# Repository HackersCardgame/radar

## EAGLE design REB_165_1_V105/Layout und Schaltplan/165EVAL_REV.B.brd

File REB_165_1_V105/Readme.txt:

1. Installieren Sie den USB Treiber "Treiber\MCP2200 Windows Driver 2014-10-09\Driver Installation Tool"
Im Windows Geräte Manager finden Sie nun ein neues Gerät mit einem virtuellen COM-Port
2. Installieren Sie die REB165 Software über die Setup.exe (Microsoft .NET Framework 4.0 muss installiert sein)
3. Starten Sie des REB165 Software und verbinden Sie sich mit dem richtigen COM-Port

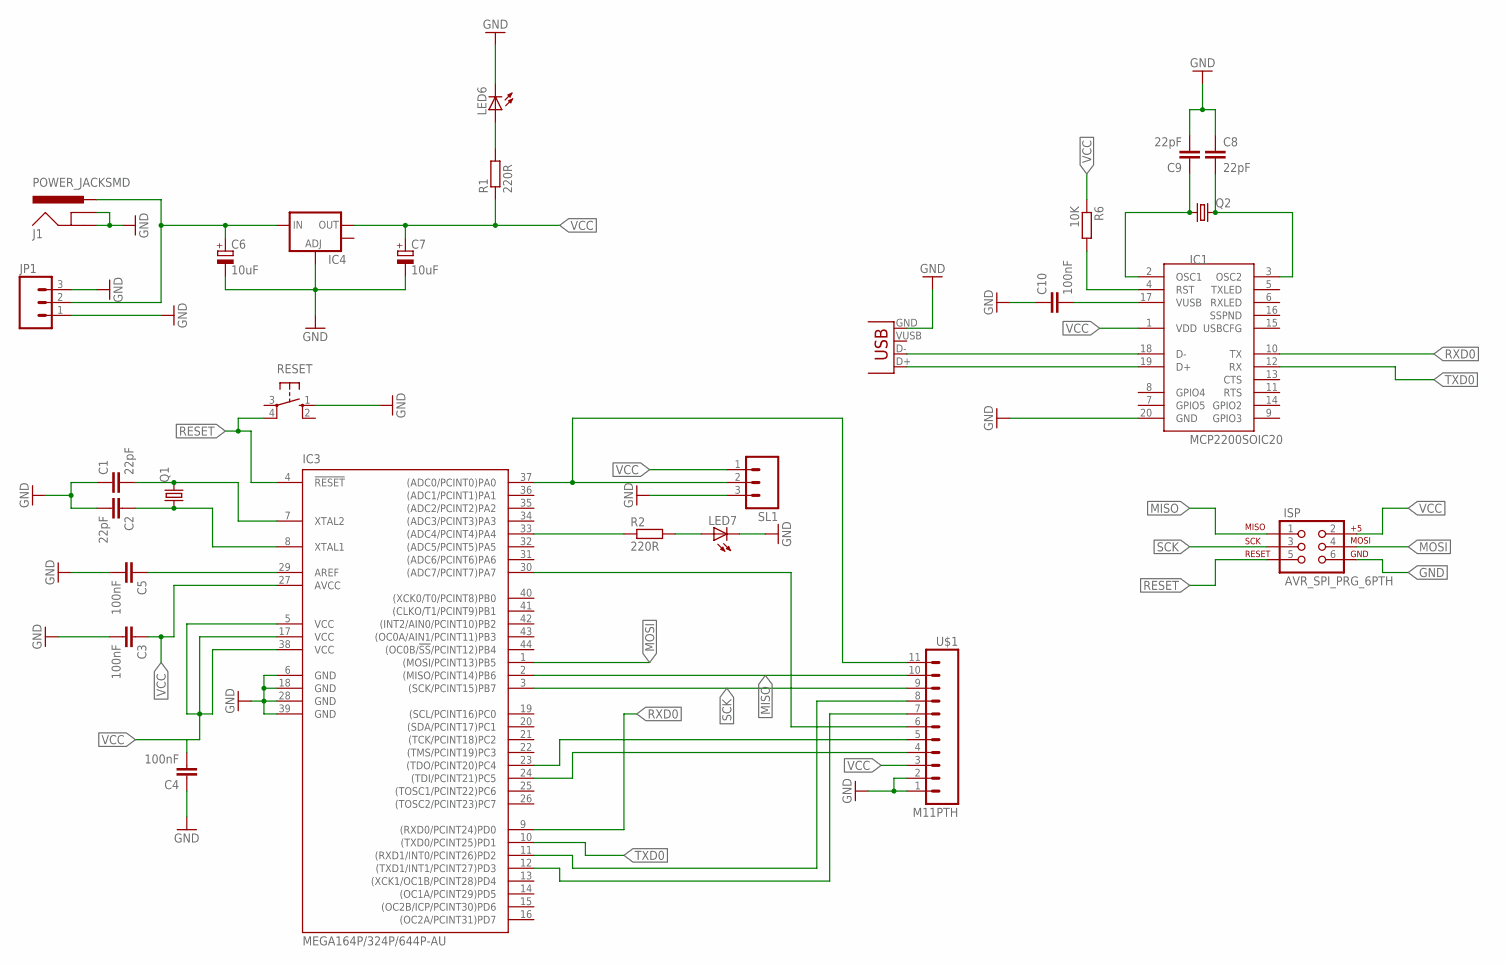
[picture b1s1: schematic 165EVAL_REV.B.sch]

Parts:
C1, C2, C8, C9: 22pF; C0805K
C3, C4, C5, C10: 100nF; C0805K
C6, C7: 10uF; CT6032
IC1: MCP2200SOIC20; SOIC20
IC3: MEGA164P/324P/644P-AU; TQFP44
IC4: V_REG_LM1117SOT223; SOT223
ISP: AVR_SPI_PRG_6PTH; 2X3
J1: POWER_JACKSMD; POWER_JACK_SMD
JP1: M03PTH; 1X03
LED6, LED7: LEDSMT1206; 1206
Q1, Q2: CRYSTALSM49; SM49
R1, R2: 220R; R1206
R6: 10K; R1206
RESET: 10-XX; B3F-10XX
SL1: M03; 03P
U$1: M11PTH; 1X11
USB: USB-B-S; USB-B-SMT

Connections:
GND: C1.1, C2.2, C3.2, C4.1, C5.2, C6.-, C7.-, C8.1, C9.2, C10.1, IC1.20 (GND), IC3.6 (GND), IC3.18 (GND), IC3.28 (GND), IC3.39 (GND), IC4.1 (ADJ), ISP.6, J1.GND (GNDBREAK), J1.P$4 (GND), JP1.1, JP1.3, LED6.C, LED7.C, RESET.1 (S), SL1.3, U$1.1, U$1.2, USB.GND
MISO: IC3.2 ((MISO/PCINT14)PB6), ISP.1, U$1.10
MOSI: IC3.1 ((MOSI/PCINT13)PB5), ISP.4
unnamed: C1.2, IC3.7 (XTAL2), Q1.2
unnamed: C2.1, IC3.8 (XTAL1), Q1.1
unnamed: C8.2, IC1.3 (OSC2), Q2.2
unnamed: C9.1, IC1.2 (OSC1), Q2.1
unnamed: IC3.37 ((ADC0/PCINT0)PA0), SL1.2, U$1.11
unnamed: C5.1, IC3.29 (AREF)
unnamed: C10.2, IC1.17 (VUSB)
unnamed: IC1.18 (D-), USB.D-
unnamed: IC1.19 (D+), USB.D+
unnamed: IC1.4 (RST), R6.2
unnamed: IC3.33 ((ADC4/PCINT4)PA4), R2.1
unnamed: IC3.11 ((RXD1/INT0/PCINT26)PD2), U$1.8
unnamed: IC3.12 ((TXD1/INT1/PCINT27)PD3), U$1.7
unnamed: IC3.30 ((ADC7/PCINT7)PA7), U$1.6
unnamed: IC3.23 ((TDO/PCINT20)PC4), U$1.5
unnamed: IC3.24 ((TDI/PCINT21)PC5), U$1.4
unnamed: C6.+, IC4.3 (IN), J1.VIN0 (PWR), JP1.2
unnamed: LED6.A, R1.2
unnamed: LED7.A, R2.2
RESET: IC3.4 (!RESET), ISP.5, RESET.4 (P1)
RXD0: IC1.10 (TX), IC3.9 ((RXD0/PCINT24)PD0)
SCK: IC3.3 ((SCK/PCINT15)PB7), ISP.3, U$1.9
TXD0: IC1.12 (RX), IC3.10 ((TXD0/PCINT25)PD1)
VCC: C3.1, C4.2, C7.+, IC1.1 (VDD), IC3.5 (VCC), IC3.17 (VCC), IC3.27 (AVCC), IC3.38 (VCC), IC4.2 (OUT), ISP.2, R1.1, R6.1, SL1.1, U$1.3

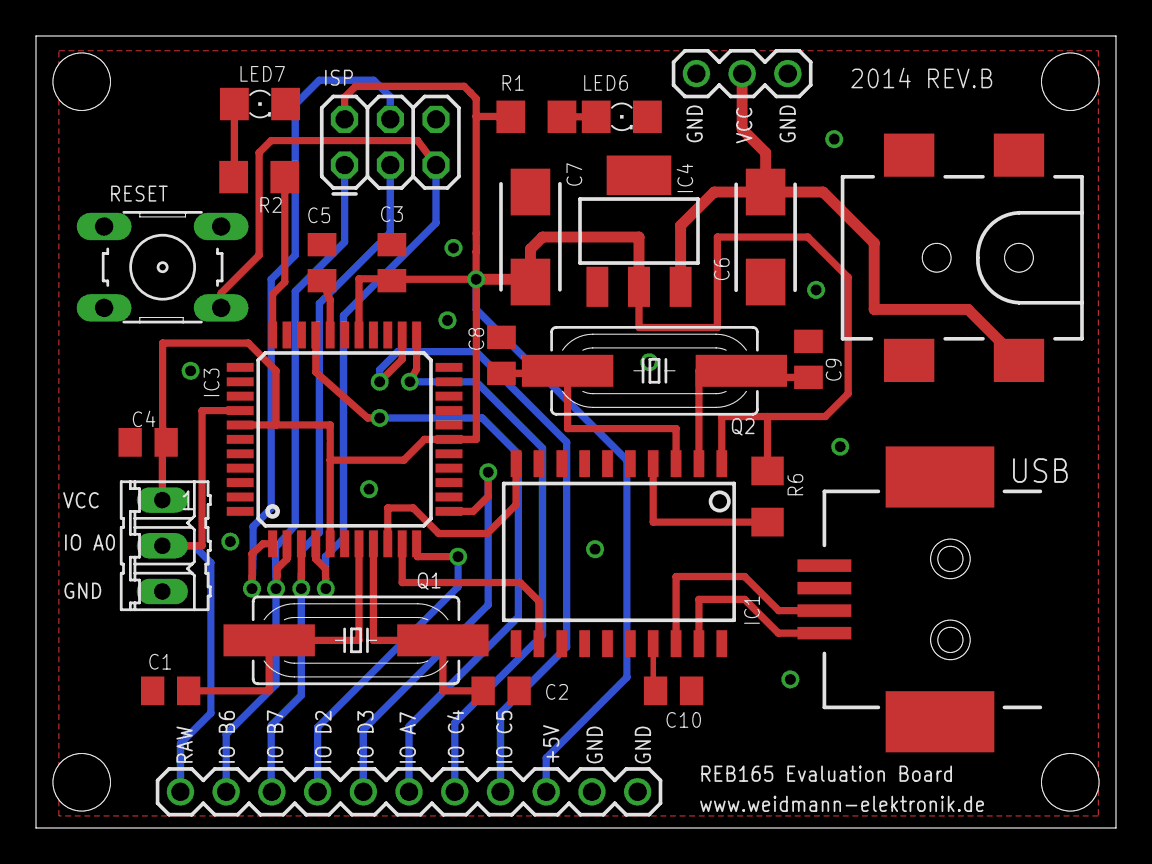
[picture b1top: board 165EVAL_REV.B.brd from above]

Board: 2 copper layers, 60.0 x 44.0 mm, 27 parts (0 on the bottom side), 27 nets.

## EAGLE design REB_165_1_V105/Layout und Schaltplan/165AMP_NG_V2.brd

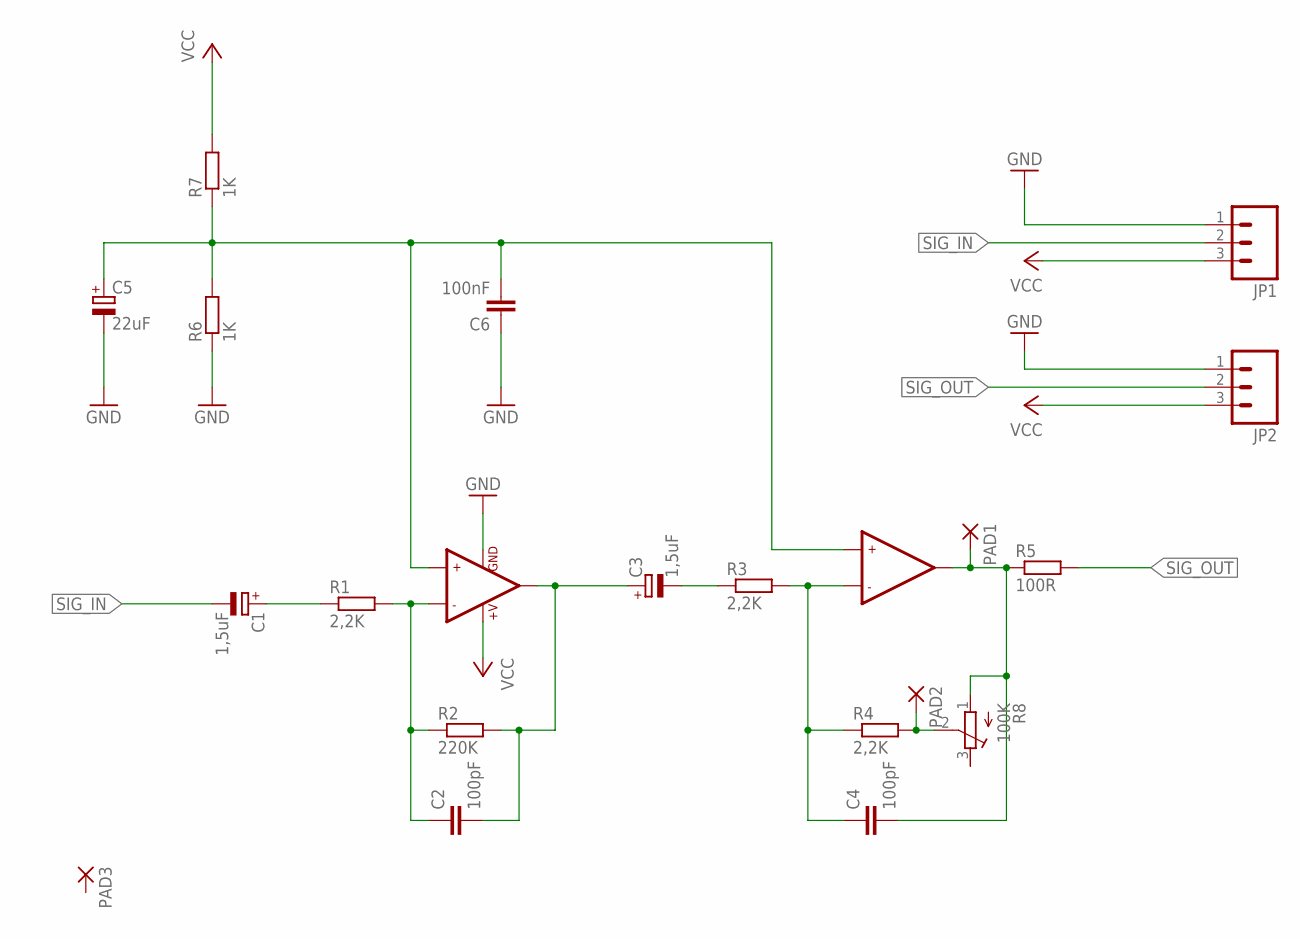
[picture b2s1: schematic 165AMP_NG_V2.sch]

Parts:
C1, C3: 1,5uF; CT6032
C2, C4: 100pF; C0805
C5: 22uF; CT6032
C6: 100nF; C0805
IC1: LMV358; SO08
JP1, JP2: M03PTH; 1X03
PAD1, PAD2, PAD3: 1,6/0,8
R1, R3, R4: 2,2K; R1206
R2: 220K; R1206
R5: 100R; R1206
R6, R7: 1K; R1206
R8: 100K; RTRIMTS63Z

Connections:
GND: C5.-, C6.1, IC1.4 (GND), JP1.1, JP2.1, R6.1
unnamed: C1.+, R1.1
unnamed: C2.1, IC1.2 (-IN1), R1.2, R2.1
unnamed: C2.2, C3.+, IC1.1 (OUT1), R2.2
unnamed: C3.-, R3.1
unnamed: C4.1, IC1.6 (-IN2), R3.2, R4.1
unnamed: C4.2, IC1.7 (OUT2), PAD1.1, R5.1, R8.1 (E)
unnamed: PAD2.1, R4.2, R8.2 (S)
unnamed: C5.+, C6.2, IC1.3 (+IN1), IC1.5 (+IN2), R6.2, R7.1
SIG_IN: C1.-, JP1.2
SIG_OUT: JP2.2, R5.2
VCC: IC1.8 (+V), JP1.3, JP2.3, R7.2

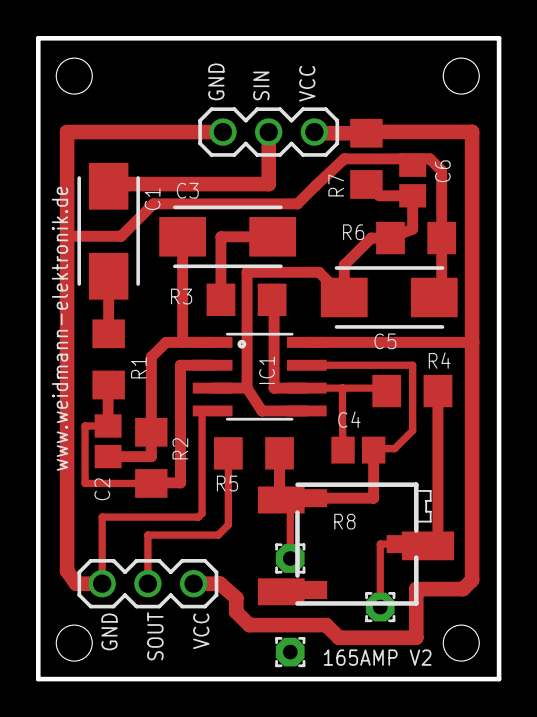
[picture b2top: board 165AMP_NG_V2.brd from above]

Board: 2 copper layers, 25.6 x 35.6 mm, 20 parts (0 on the bottom side), 12 nets.
